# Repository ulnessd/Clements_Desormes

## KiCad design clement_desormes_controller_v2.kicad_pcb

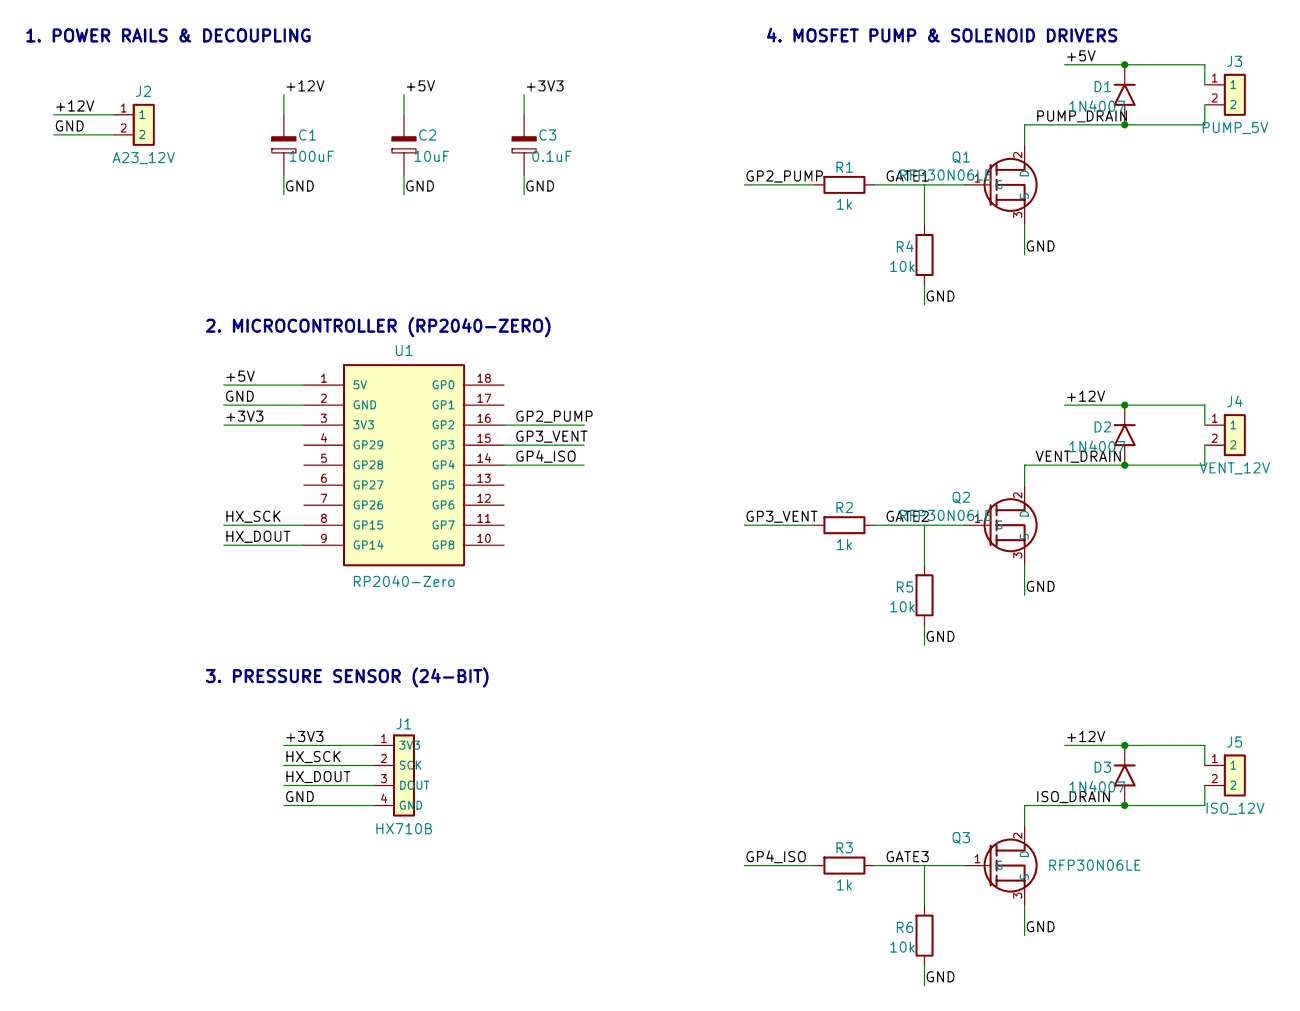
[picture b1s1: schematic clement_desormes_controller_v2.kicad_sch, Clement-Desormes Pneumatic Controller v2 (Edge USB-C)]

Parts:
C1: 100uF; CP_Radial_D5.0mm_P2.50mm
C2: 10uF; CP_Radial_D5.0mm_P2.50mm
C3: 0.1uF; CP_Radial_D5.0mm_P2.50mm
D1, D2, D3: 1N4007; D_DO-41_SOD81_P7.62mm_Horizontal
J1: HX710B; PinHeader_1x04_P2.54mm_Vertical
J2: A23_12V; TerminalBlock_Phoenix_MKDS-1,5-2-5.08_1x02_P5.08mm_Horizont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
J3: PUMP_5V; TerminalBlock_Phoenix_MKDS-1,5-2-5.08_1x02_P5.08mm_Horizont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
J4: VENT_12V; TerminalBlock_Phoenix_MKDS-1,5-2-5.08_1x02_P5.08mm_Horizont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
J5: ISO_12V; TerminalBlock_Phoenix_MKDS-1,5-2-5.08_1x02_P5.08mm_Horizont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
Q1, Q2, Q3: RFP30N06LE; TO-220-3_Vertical
R1, R2, R3: 1k; R_Axial_DIN0207_L6.3mm_D2.5mm_P7.62mm
R4, R5, R6: 10k; R_Axial_DIN0207_L6.3mm_D2.5mm_P7.62mm
U1: RP2040-Zero; Waveshare_RP2040_Zero

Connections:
+3V3: C3.1, J1.1 (3V3), U1.3 (3V3)
+5V: C2.1, D1.1 (K), J3.1, U1.1 (5V)
+12V: C1.1, D2.1 (K), D3.1 (K), J2.1, J4.1, J5.1
GATE1: Q1.1 (G), R1.2, R4.1
GATE2: Q2.1 (G), R2.2, R5.1
GATE3: Q3.1 (G), R3.2, R6.1
GND: C1.2, C2.2, C3.2, J1.4 (GND), J2.2, Q1.3 (S), Q2.3 (S), Q3.3 (S), R4.2, R5.2, R6.2, U1.2 (GND)
GP2_PUMP: R1.1, U1.16 (GP2)
GP3_VENT: R2.1, U1.15 (GP3)
GP4_ISO: R3.1, U1.14 (GP4)
HX_DOUT: J1.3 (DOUT), U1.9 (GP14)
HX_SCK: J1.2 (SCK), U1.8 (GP15)
ISO_DRAIN: D3.2 (A), J5.2, Q3.2 (D)
PUMP_DRAIN: D1.2 (A), J3.2, Q1.2 (D)
VENT_DRAIN: D2.2 (A), J4.2, Q2.2 (D)

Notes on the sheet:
2. MICROCONTROLLER (RP2040-ZERO)
1. POWER RAILS & DECOUPLING
3. PRESSURE SENSOR (24-BIT)
4. MOSFET PUMP & SOLENOID DRIVERS

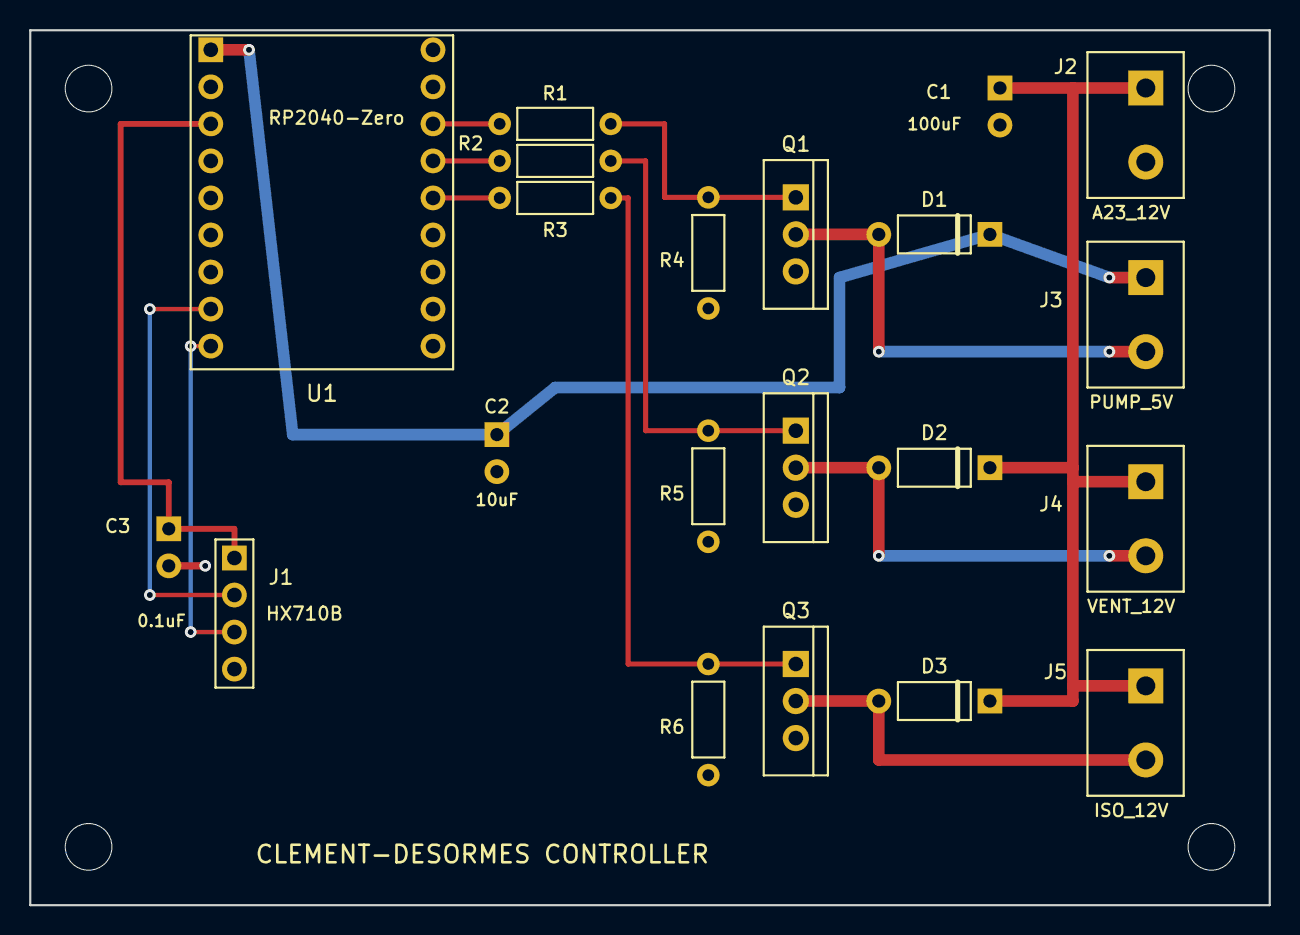
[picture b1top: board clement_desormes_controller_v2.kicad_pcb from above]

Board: 2 copper layers, 85.0 x 60.0 mm, 21 parts (0 on the bottom side), 15 nets.
